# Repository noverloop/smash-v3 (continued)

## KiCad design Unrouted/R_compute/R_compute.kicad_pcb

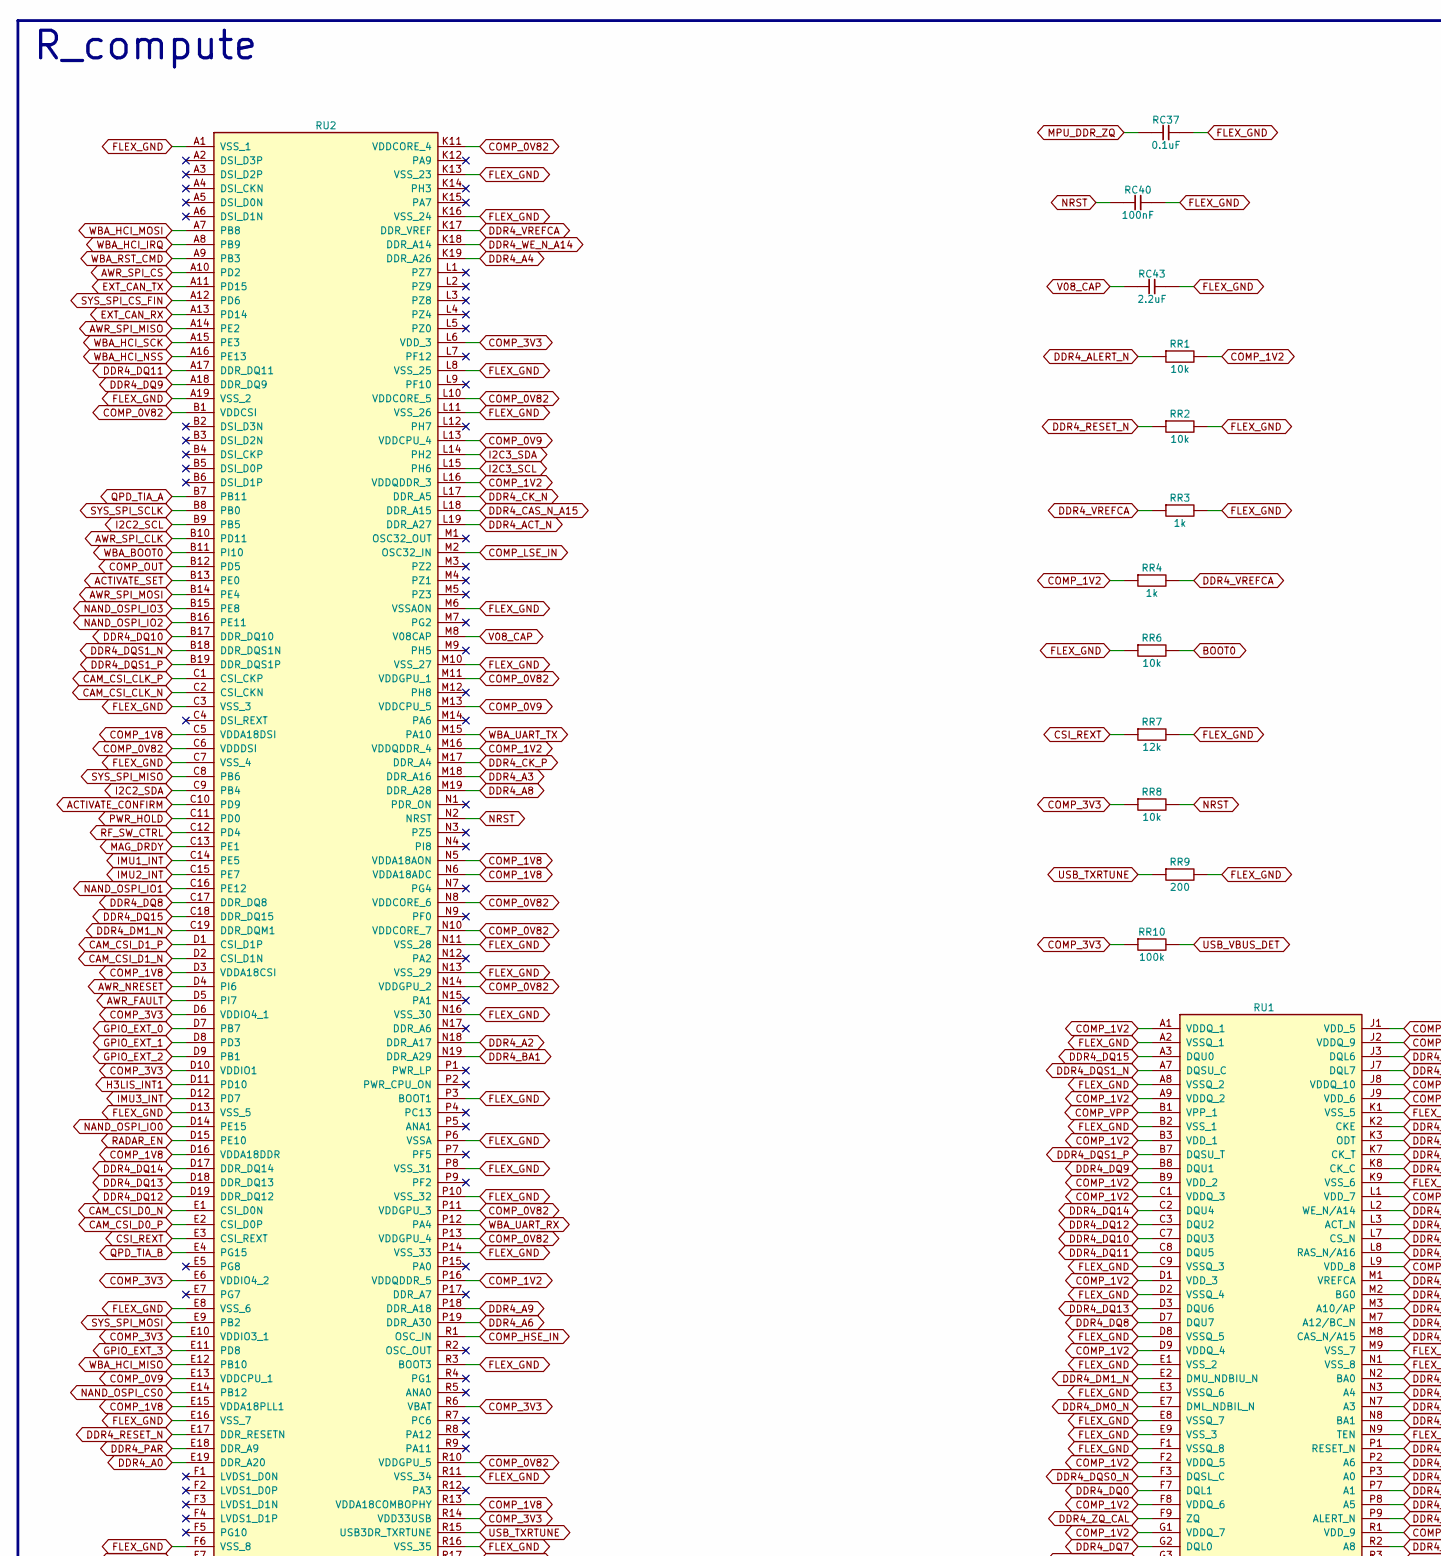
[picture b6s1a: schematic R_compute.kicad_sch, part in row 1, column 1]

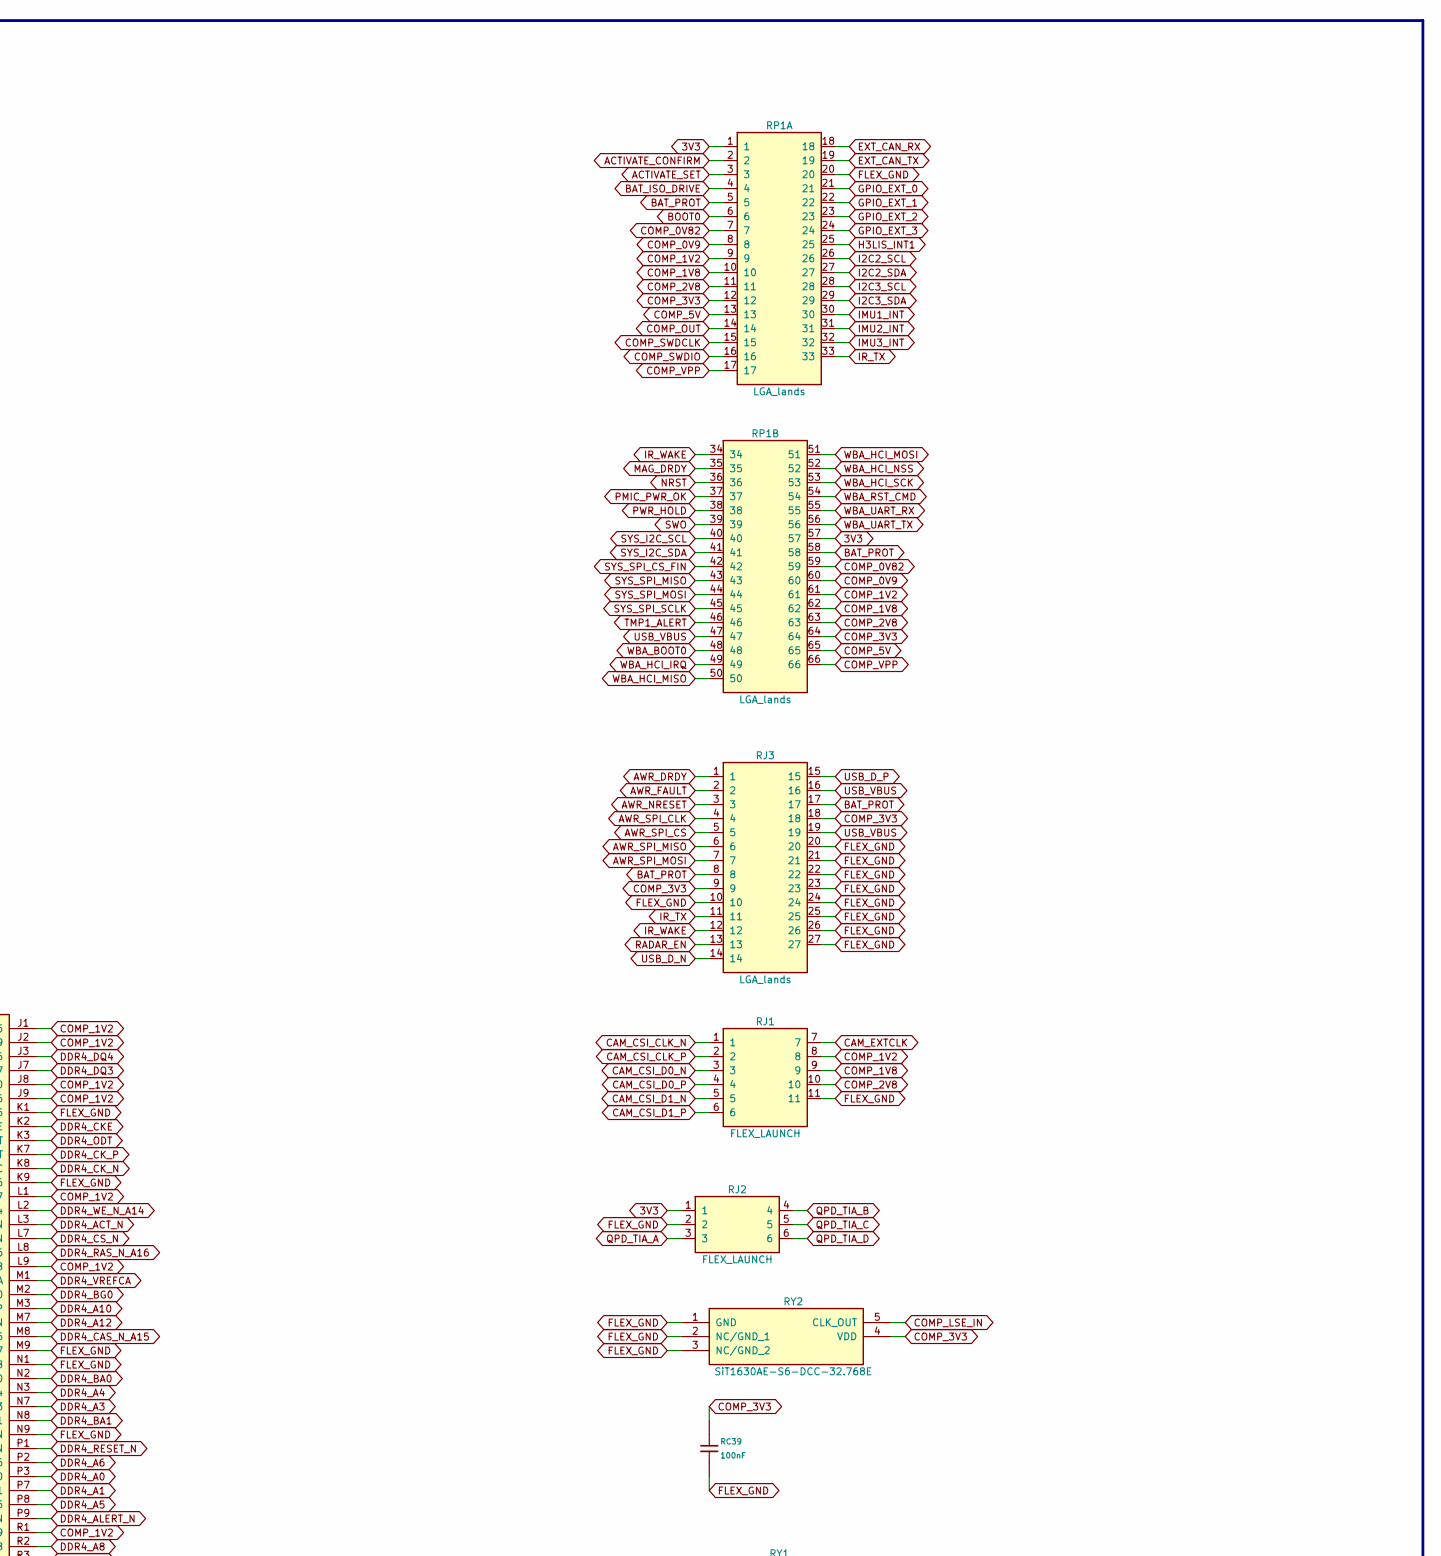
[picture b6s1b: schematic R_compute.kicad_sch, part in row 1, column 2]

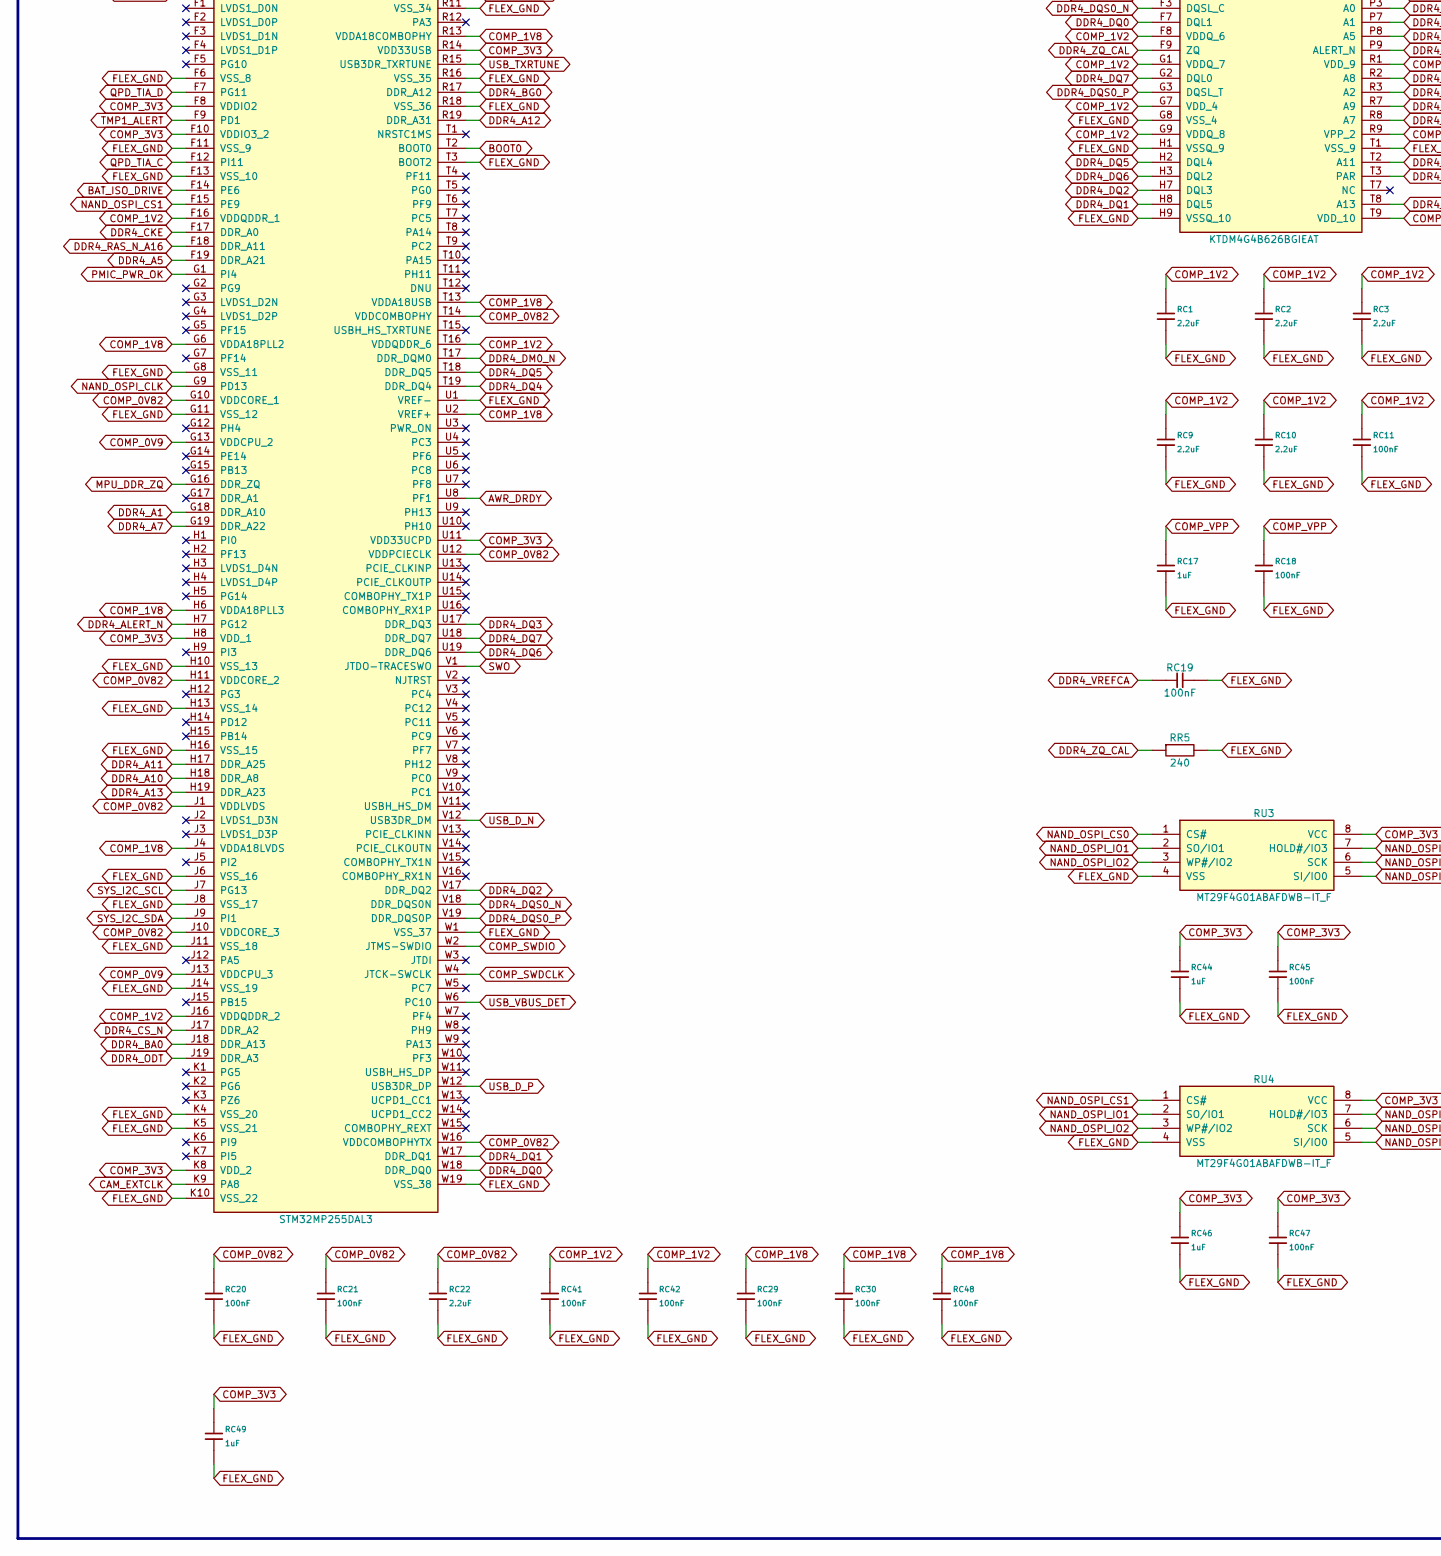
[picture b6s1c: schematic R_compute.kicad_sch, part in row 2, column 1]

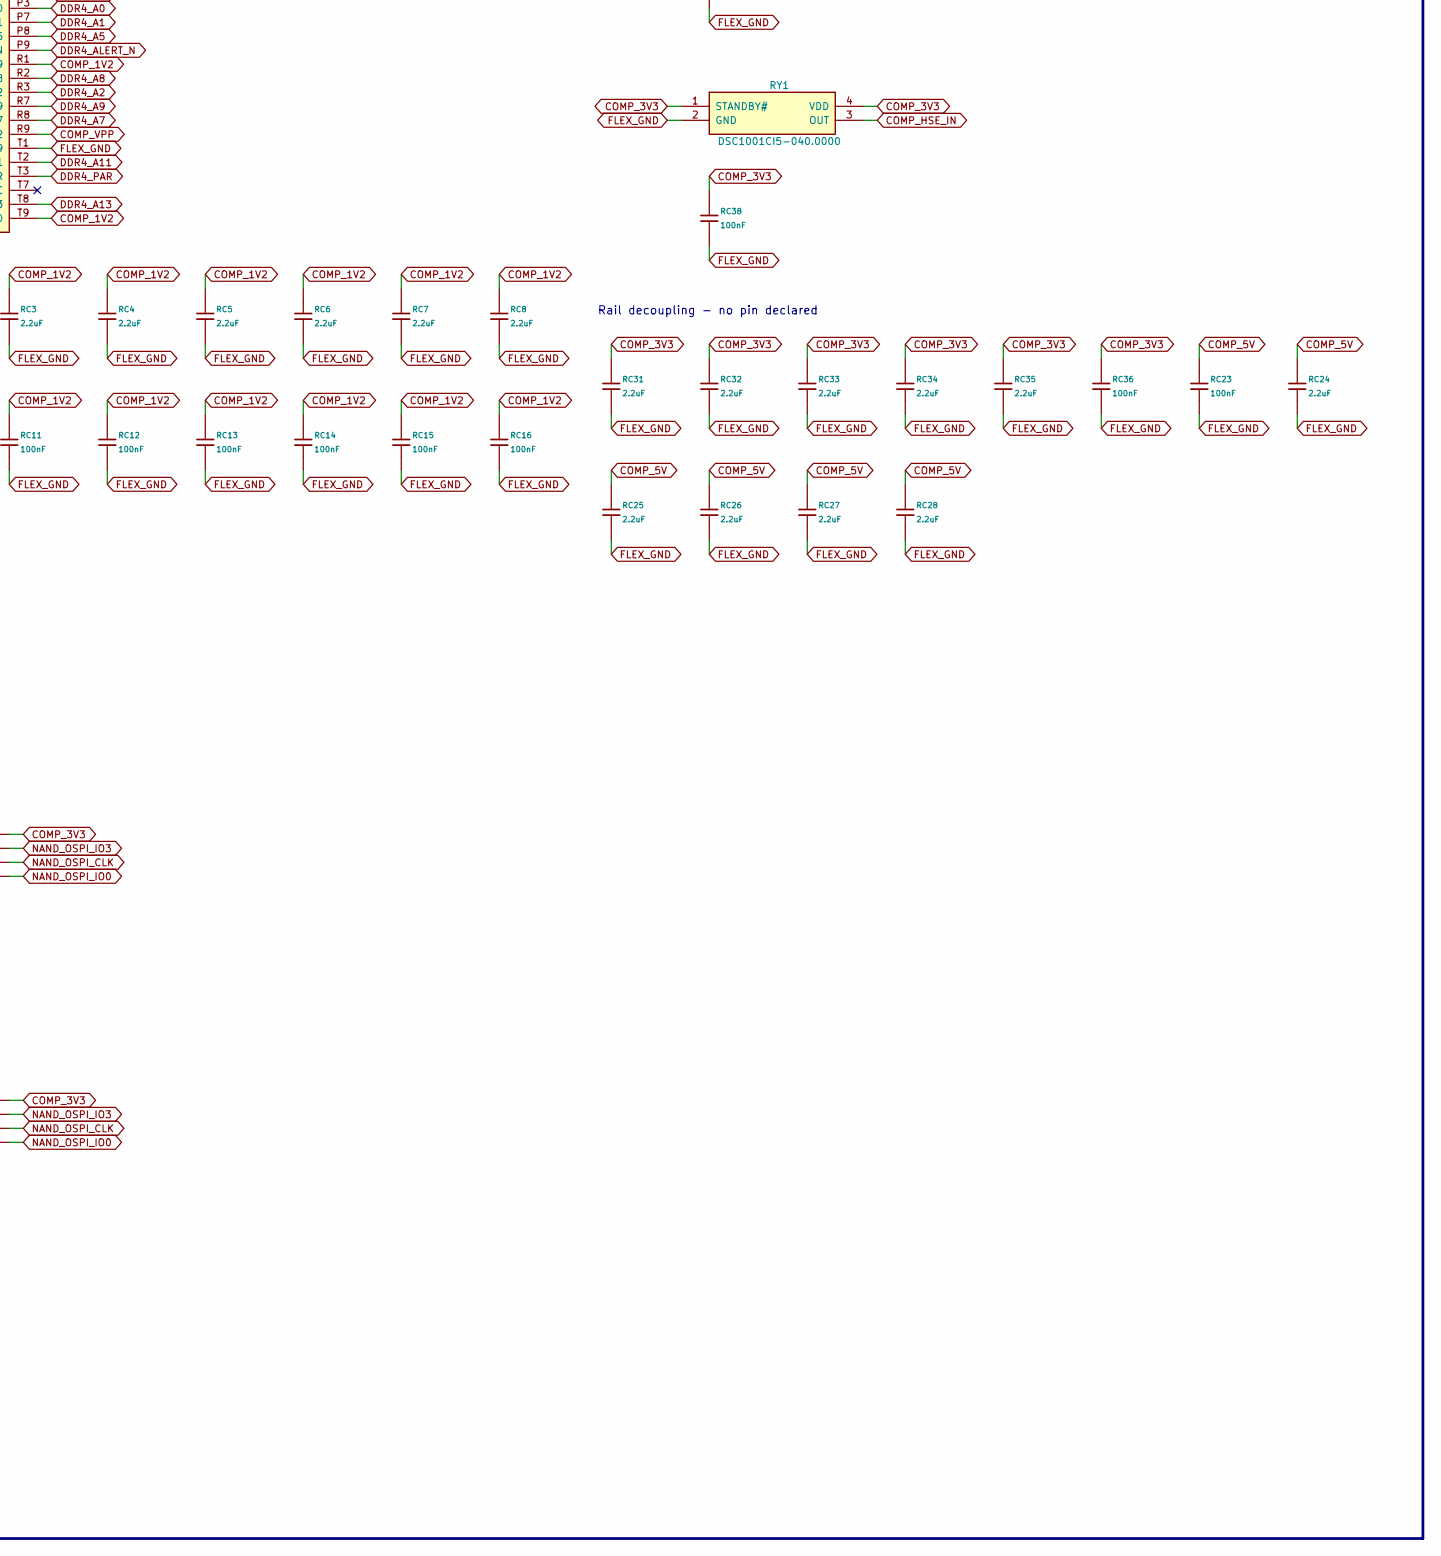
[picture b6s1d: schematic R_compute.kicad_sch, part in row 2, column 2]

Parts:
RC1, RC2, RC3, RC4, RC5, RC6, RC7, RC8, RC9, RC10, RC22, RC24, RC25, RC26, RC27, RC28, RC31, RC32, RC33, RC34, RC35, RC43: 2.2uF; Capacitor_SMD_C_0603_1608Metric; MPN C-Series MIL-PRF-32535 X7R 0603 2.2uF
RC11, RC12, RC13, RC14, RC15, RC16, RC18, RC19, RC20, RC21, RC23, RC29, RC30, RC36, RC38, RC39, RC40, RC41, RC42, RC45, RC47, RC48: 100nF; Capacitor_SMD_C_0402_1005Metric; MPN C0402 X7R 100nF
RC17, RC44, RC46, RC49: 1uF; Capacitor_SMD_C_0805_2012Metric; MPN C-Series MIL-PRF-32535 X7R 0805 1uF
RC37: 0.1uF; Capacitor_SMD_C_0402_1005Metric; MPN C0402 X7R 0.1uF
RJ1: FLEX_LAUNCH; J_FLEXL_companion_compute__camera_module; MPN FLEX_LAUNCH
RJ2: FLEX_LAUNCH; J_FLEXL_companion_compute__qpd_module; MPN FLEX_LAUNCH
RJ3: LGA_lands; J_companion_compute_spacer_companion_compute_radar_module; MPN LGA_lands
RP1: LGA_lands; P_companion_compute_spacer_power_board_companion_compute; MPN LGA_lands
RR1, RR2, RR6, RR8: 10k; Resistor_SMD_R_0402_1005Metric; MPN CRCW0402 10k 1% e3
RR3, RR4: 1k; Resistor_SMD_R_0402_1005Metric; MPN CRCW0402 1k 1% e3
RR5: 240; Resistor_SMD_R_0402_1005Metric; MPN CRCW0402 240 1% e3
RR7: 12k; Resistor_SMD_R_0402_1005Metric; MPN CRCW0402 12k 1% e3
RR9: 200; Resistor_SMD_R_0402_1005Metric; MPN CRCW0402 200 1% e3
RR10: 100k; Resistor_SMD_R_0402_1005Metric; MPN CRCW0402 100k 1% e3
RU1: KTDM4G4B626BGIEAT; BGA96C80P9X16_750X1300X100; MPN KTDM4G4B626BGIEAT
RU2: STM32MP255DAL3; MPN STM32MP255DAL3
RU3, RU4: MT29F4G01ABAFDWB-IT_F; SON127P800X600X65-8N; MPN MT29F4G01ABAFDWB-IT_F
RY1: DSC1001CI5-040.0000; DSC1001CI50080000; MPN DSC1001CI5-040.0000
RY2: SiT1630AE-S6-DCC-32.768E; SOT-23_5pins; MPN SiT1630AE-S6-DCC-32.768E

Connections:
3V3: RJ2.1, RP1.1, RP1.57
ACTIVATE_CONFIRM: RP1.2, RU2.C10 (PD9)
ACTIVATE_SET: RP1.3, RU2.B13 (PE0)
AWR_DRDY: RJ3.1, RU2.U8 (PF1)
AWR_FAULT: RJ3.2, RU2.D5 (PI7)
AWR_NRESET: RJ3.3, RU2.D4 (PI6)
AWR_SPI_CLK: RJ3.4, RU2.B10 (PD11)
AWR_SPI_CS: RJ3.5, RU2.A10 (PD2)
AWR_SPI_MISO: RJ3.6, RU2.A14 (PE2)
AWR_SPI_MOSI: RJ3.7, RU2.B14 (PE4)
BAT_ISO_DRIVE: RP1.4, RU2.F14 (PE6)
BAT_PROT: RJ3.8, RJ3.17, RP1.5, RP1.58
BOOT0: RP1.6, RR6.2, RU2.T2 (BOOT0)
CAM_CSI_CLK_N: RJ1.1, RU2.C2 (CSI_CKN)
CAM_CSI_CLK_P: RJ1.2, RU2.C1 (CSI_CKP)
CAM_CSI_D0_N: RJ1.3, RU2.E1 (CSI_D0N)
CAM_CSI_D0_P: RJ1.4, RU2.E2 (CSI_D0P)
CAM_CSI_D1_N: RJ1.5, RU2.D2 (CSI_D1N)
CAM_CSI_D1_P: RJ1.6, RU2.D1 (CSI_D1P)
CAM_EXTCLK: RJ1.7, RU2.K9 (PA8)
COMP_0V9: RP1.8, RP1.60, RU2.E13 (VDDCPU_1), RU2.G13 (VDDCPU_2), RU2.J13 (VDDCPU_3), RU2.L13 (VDDCPU_4), RU2.M13 (VDDCPU_5)
COMP_0V82: RC20.1, RC21.1, RC22.1, RP1.7, RP1.59, RU2.B1 (VDDCSI), RU2.C6 (VDDDSI), RU2.G10 (VDDCORE_1), RU2.H11 (VDDCORE_2), RU2.J1 (VDDLVDS), RU2.J10 (VDDCORE_3), RU2.K11 (VDDCORE_4), RU2.L10 (VDDCORE_5), RU2.M11 (VDDGPU_1), RU2.N8 (VDDCORE_6), RU2.N10 (VDDCORE_7), RU2.N14 (VDDGPU_2), RU2.P11 (VDDGPU_3), RU2.P13 (VDDGPU_4), RU2.R10 (VDDGPU_5), RU2.T14 (VDDCOMBOPHY), RU2.U12 (VDDPCIECLK), RU2.W16 (VDDCOMBOPHYTX)
COMP_1V2: RC1.1, RC2.1, RC3.1, RC4.1, RC5.1, RC6.1, RC7.1, RC8.1, RC9.1, RC10.1, RC11.1, RC12.1, RC13.1, RC14.1, RC15.1, RC16.1, RC41.1, RC42.1, RJ1.8, RP1.9, RP1.61, RR1.2, RR4.1, RU1.A1 (VDDQ_1), RU1.A9 (VDDQ_2), RU1.B3 (VDD_1), RU1.B9 (VDD_2), RU1.C1 (VDDQ_3), RU1.D1 (VDD_3), RU1.D9 (VDDQ_4), RU1.F2 (VDDQ_5), RU1.F8 (VDDQ_6), RU1.G1 (VDDQ_7), RU1.G7 (VDD_4), RU1.G9 (VDDQ_8), RU1.J1 (VDD_5), RU1.J2 (VDDQ_9), RU1.J8 (VDDQ_10), RU1.J9 (VDD_6), RU1.L1 (VDD_7), RU1.L9 (VDD_8), RU1.R1 (VDD_9), RU1.T9 (VDD_10), RU2.F16 (VDDQDDR_1), RU2.J16 (VDDQDDR_2), RU2.L16 (VDDQDDR_3), RU2.M16 (VDDQDDR_4), RU2.P16 (VDDQDDR_5), RU2.T16 (VDDQDDR_6)
COMP_1V8: RC29.1, RC30.1, RC48.1, RJ1.9, RP1.10, RP1.62, RU2.C5 (VDDA18DSI), RU2.D3 (VDDA18CSI), RU2.D16 (VDDA18DDR), RU2.E15 (VDDA18PLL1), RU2.G6 (VDDA18PLL2), RU2.H6 (VDDA18PLL3), RU2.J4 (VDDA18LVDS), RU2.N5 (VDDA18AON), RU2.N6 (VDDA18ADC), RU2.R13 (VDDA18COMBOPHY), RU2.T13 (VDDA18USB), RU2.U2 (VREF+)
COMP_2V8: RJ1.10, RP1.11, RP1.63
COMP_3V3: RC31.1, RC32.1, RC33.1, RC34.1, RC35.1, RC36.1, RC38.1, RC39.1, RC44.1, RC45.1, RC46.1, RC47.1, RC49.1, RJ3.9, RJ3.18, RP1.12, RP1.64, RR8.1, RR10.1, RU2.D6 (VDDIO4_1), RU2.D10 (VDDIO1), RU2.E6 (VDDIO4_2), RU2.E10 (VDDIO3_1), RU2.F8 (VDDIO2), RU2.F10 (VDDIO3_2), RU2.H8 (VDD_1), RU2.K8 (VDD_2), RU2.L6 (VDD_3), RU2.R6 (VBAT), RU2.R14 (VDD33USB), RU2.U11 (VDD33UCPD), RU3.8 (VCC), RU4.8 (VCC), RY1.1 (STANDBY#), RY1.4 (VDD), RY2.4 (VDD)
COMP_5V: RC23.1, RC24.1, RC25.1, RC26.1, RC27.1, RC28.1, RP1.13, RP1.65
COMP_HSE_IN: RU2.R1 (OSC_IN), RY1.3 (OUT)
COMP_LSE_IN: RU2.M2 (OSC32_IN), RY2.5 (CLK_OUT)
COMP_OUT: RP1.14, RU2.B12 (PD5)
COMP_SWDCLK: RP1.15, RU2.W4 (JTCK-SWCLK)
COMP_SWDIO: RP1.16, RU2.W2 (JTMS-SWDIO)
COMP_VPP: RC17.1, RC18.1, RP1.17, RP1.66, RU1.B1 (VPP_1), RU1.R9 (VPP_2)
CSI_REXT: RR7.1, RU2.E3 (CSI_REXT)
DDR4_A0: RU1.P3 (A0), RU2.E19 (DDR_A20)
DDR4_A1: RU1.P7 (A1), RU2.G18 (DDR_A10)
DDR4_A2: RU1.R3 (A2), RU2.N18 (DDR_A17)
DDR4_A3: RU1.N7 (A3), RU2.M18 (DDR_A16)
DDR4_A4: RU1.N3 (A4), RU2.K19 (DDR_A26)
DDR4_A5: RU1.P8 (A5), RU2.F19 (DDR_A21)
DDR4_A6: RU1.P2 (A6), RU2.P19 (DDR_A30)
DDR4_A7: RU1.R8 (A7), RU2.G19 (DDR_A22)
DDR4_A8: RU1.R2 (A8), RU2.M19 (DDR_A28)
DDR4_A9: RU1.R7 (A9), RU2.P18 (DDR_A18)
DDR4_A10: RU1.M3 (A10/AP), RU2.H18 (DDR_A8)
DDR4_A11: RU1.T2 (A11), RU2.H17 (DDR_A25)
DDR4_A12: RU1.M7 (A12/BC_N), RU2.R19 (DDR_A31)
DDR4_A13: RU1.T8 (A13), RU2.H19 (DDR_A23)
DDR4_ACT_N: RU1.L3 (ACT_N), RU2.L19 (DDR_A27)
DDR4_ALERT_N: RR1.1, RU1.P9 (ALERT_N), RU2.H7 (PG12)
DDR4_BA0: RU1.N2 (BA0), RU2.J18 (DDR_A13)
DDR4_BA1: RU1.N8 (BA1), RU2.N19 (DDR_A29)
DDR4_BG0: RU1.M2 (BG0), RU2.R17 (DDR_A12)
DDR4_CAS_N_A15: RU1.M8 (CAS_N/A15), RU2.L18 (DDR_A15)
DDR4_CKE: RU1.K2 (CKE), RU2.F17 (DDR_A0)
DDR4_CK_N: RU1.K8 (CK_C), RU2.L17 (DDR_A5)
DDR4_CK_P: RU1.K7 (CK_T), RU2.M17 (DDR_A4)
DDR4_CS_N: RU1.L7 (CS_N), RU2.J17 (DDR_A2)
DDR4_DM0_N: RU1.E7 (DML_NDBIL_N), RU2.T17 (DDR_DQM0)
DDR4_DM1_N: RU1.E2 (DMU_NDBIU_N), RU2.C19 (DDR_DQM1)
DDR4_DQ0: RU1.F7 (DQL1), RU2.W18 (DDR_DQ0)
DDR4_DQ1: RU1.H8 (DQL5), RU2.W17 (DDR_DQ1)
DDR4_DQ2: RU1.H7 (DQL3), RU2.V17 (DDR_DQ2)
DDR4_DQ3: RU1.J7 (DQL7), RU2.U17 (DDR_DQ3)
DDR4_DQ4: RU1.J3 (DQL6), RU2.T19 (DDR_DQ4)
DDR4_DQ5: RU1.H2 (DQL4), RU2.T18 (DDR_DQ5)
DDR4_DQ6: RU1.H3 (DQL2), RU2.U19 (DDR_DQ6)
DDR4_DQ7: RU1.G2 (DQL0), RU2.U18 (DDR_DQ7)
DDR4_DQ8: RU1.D7 (DQU7), RU2.C17 (DDR_DQ8)
DDR4_DQ9: RU1.B8 (DQU1), RU2.A18 (DDR_DQ9)
DDR4_DQ10: RU1.C7 (DQU3), RU2.B17 (DDR_DQ10)
DDR4_DQ11: RU1.C8 (DQU5), RU2.A17 (DDR_DQ11)
DDR4_DQ12: RU1.C3 (DQU2), RU2.D19 (DDR_DQ12)
DDR4_DQ13: RU1.D3 (DQU6), RU2.D18 (DDR_DQ13)
DDR4_DQ14: RU1.C2 (DQU4), RU2.D17 (DDR_DQ14)
DDR4_DQ15: RU1.A3 (DQU0), RU2.C18 (DDR_DQ15)
DDR4_DQS0_N: RU1.F3 (DQSL_C), RU2.V18 (DDR_DQS0N)
DDR4_DQS0_P: RU1.G3 (DQSL_T), RU2.V19 (DDR_DQS0P)
DDR4_DQS1_N: RU1.A7 (DQSU_C), RU2.B18 (DDR_DQS1N)
DDR4_DQS1_P: RU1.B7 (DQSU_T), RU2.B19 (DDR_DQS1P)
DDR4_ODT: RU1.K3 (ODT), RU2.J19 (DDR_A3)
DDR4_PAR: RU1.T3 (PAR), RU2.E18 (DDR_A9)
DDR4_RAS_N_A16: RU1.L8 (RAS_N/A16), RU2.F18 (DDR_A11)
DDR4_RESET_N: RR2.1, RU1.P1 (RESET_N), RU2.E17 (DDR_RESETN)
DDR4_VREFCA: RC19.1, RR3.1, RR4.2, RU1.M1 (VREFCA), RU2.K17 (DDR_VREF)
DDR4_WE_N_A14: RU1.L2 (WE_N/A14), RU2.K18 (DDR_A14)
DDR4_ZQ_CAL: RR5.1, RU1.F9 (ZQ)
EXT_CAN_RX: RP1.18, RU2.A13 (PD14)
EXT_CAN_TX: RP1.19, RU2.A11 (PD15)
FLEX_GND: RC1.2, RC2.2, RC3.2, RC4.2, RC5.2, RC6.2, RC7.2, RC8.2, RC9.2, RC10.2, RC11.2, RC12.2, RC13.2, RC14.2, RC15.2, RC16.2, RC17.2, RC18.2, RC19.2, RC20.2, RC21.2, RC22.2, RC23.2, RC24.2, RC25.2, RC26.2, RC27.2, RC28.2, RC29.2, RC30.2, RC31.2, RC32.2, RC33.2, RC34.2, RC35.2, RC36.2, RC37.2, RC38.2, RC39.2, RC40.2, RC41.2, RC42.2, RC43.2, RC44.2, RC45.2, RC46.2, RC47.2, RC48.2, RC49.2, RJ1.11, RJ2.2, RJ3.10, RJ3.20, RJ3.21, RJ3.22, RJ3.23, RJ3.24, RJ3.25, RJ3.26, RJ3.27, RP1.20, RR2.2, RR3.2, RR5.2, RR6.1, RR7.2, RR9.2, RU1.A2 (VSSQ_1), RU1.A8 (VSSQ_2), RU1.B2 (VSS_1), RU1.C9 (VSSQ_3), RU1.D2 (VSSQ_4), RU1.D8 (VSSQ_5), RU1.E1 (VSS_2), RU1.E3 (VSSQ_6), RU1.E8 (VSSQ_7), RU1.E9 (VSS_3), RU1.F1 (VSSQ_8), RU1.G8 (VSS_4), RU1.H1 (VSSQ_9), RU1.H9 (VSSQ_10), RU1.K1 (VSS_5), RU1.K9 (VSS_6), RU1.M9 (VSS_7), RU1.N1 (VSS_8), RU1.N9 (TEN), RU1.T1 (VSS_9), RU2.A1 (VSS_1), RU2.A19 (VSS_2), RU2.C3 (VSS_3), RU2.C7 (VSS_4), RU2.D13 (VSS_5), RU2.E8 (VSS_6), RU2.E16 (VSS_7), RU2.F6 (VSS_8), RU2.F11 (VSS_9), RU2.F13 (VSS_10), RU2.G8 (VSS_11), RU2.G11 (VSS_12), RU2.H10 (VSS_13), RU2.H13 (VSS_14), RU2.H16 (VSS_15), RU2.J6 (VSS_16), RU2.J8 (VSS_17), RU2.J11 (VSS_18), RU2.J14 (VSS_19), RU2.K4 (VSS_20), RU2.K5 (VSS_21), RU2.K10 (VSS_22), RU2.K13 (VSS_23), RU2.K16 (VSS_24), RU2.L8 (VSS_25), RU2.L11 (VSS_26), RU2.M6 (VSSAON), RU2.M10 (VSS_27), RU2.N11 (VSS_28), RU2.N13 (VSS_29), RU2.N16 (VSS_30), RU2.P3 (BOOT1), RU2.P6 (VSSA), RU2.P8 (VSS_31), RU2.P10 (VSS_32), RU2.P14 (VSS_33), RU2.R3 (BOOT3), RU2.R11 (VSS_34), RU2.R16 (VSS_35), RU2.R18 (VSS_36), RU2.T3 (BOOT2), RU2.U1 (VREF-), RU2.W1 (VSS_37), RU2.W19 (VSS_38), RU3.4 (VSS), RU4.4 (VSS), RY1.2 (GND), RY2.1 (GND), RY2.2 (NC/GND_1), RY2.3 (NC/GND_2)
GPIO_EXT_0: RP1.21, RU2.D7 (PB7)
GPIO_EXT_1: RP1.22, RU2.D8 (PD3)
GPIO_EXT_2: RP1.23, RU2.D9 (PB1)
GPIO_EXT_3: RP1.24, RU2.E11 (PD8)
H3LIS_INT1: RP1.25, RU2.D11 (PD10)
I2C2_SCL: RP1.26, RU2.B9 (PB5)
I2C2_SDA: RP1.27, RU2.C9 (PB4)
I2C3_SCL: RP1.28, RU2.L15 (PH6)
I2C3_SDA: RP1.29, RU2.L14 (PH2)
IMU1_INT: RP1.30, RU2.C14 (PE5)
IMU2_INT: RP1.31, RU2.C15 (PE7)
IMU3_INT: RP1.32, RU2.D12 (PD7)
IR_TX: RJ3.11, RP1.33
IR_WAKE: RJ3.12, RP1.34
MAG_DRDY: RP1.35, RU2.C13 (PE1)
MPU_DDR_ZQ: RC37.1, RU2.G16 (DDR_ZQ)
NAND_OSPI_CLK: RU2.G9 (PD13), RU3.6 (SCK), RU4.6 (SCK)
NAND_OSPI_CS0: RU2.E14 (PB12), RU3.1 (CS#)
NAND_OSPI_CS1: RU2.F15 (PE9), RU4.1 (CS#)
NAND_OSPI_IO0: RU2.D14 (PE15), RU3.5 (SI/IO0), RU4.5 (SI/IO0)
NAND_OSPI_IO1: RU2.C16 (PE12), RU3.2 (SO/IO1), RU4.2 (SO/IO1)
NAND_OSPI_IO2: RU2.B16 (PE11), RU3.3 (WP#/IO2), RU4.3 (WP#/IO2)
NAND_OSPI_IO3: RU2.B15 (PE8), RU3.7 (HOLD#/IO3), RU4.7 (HOLD#/IO3)
NRST: RC40.1, RP1.36, RR8.2, RU2.N2 (NRST)
PMIC_PWR_OK: RP1.37, RU2.G1 (PI4)
PWR_HOLD: RP1.38, RU2.C11 (PD0)
QPD_TIA_A: RJ2.3, RU2.B7 (PB11)
QPD_TIA_B: RJ2.4, RU2.E4 (PG15)
QPD_TIA_C: RJ2.5, RU2.F12 (PI11)
QPD_TIA_D: RJ2.6, RU2.F7 (PG11)
RADAR_EN: RJ3.13, RU2.D15 (PE10)
RF_SW_CTRL: RU2.C12 (PD4)
SWO: RP1.39, RU2.V1 (JTDO-TRACESWO)
SYS_I2C_SCL: RP1.40, RU2.J7 (PG13)
SYS_I2C_SDA: RP1.41, RU2.J9 (PI1)
SYS_SPI_CS_FIN: RP1.42, RU2.A12 (PD6)
SYS_SPI_MISO: RP1.43, RU2.C8 (PB6)
SYS_SPI_MOSI: RP1.44, RU2.E9 (PB2)
SYS_SPI_SCLK: RP1.45, RU2.B8 (PB0)
TMP1_ALERT: RP1.46, RU2.F9 (PD1)
USB_D_N: RJ3.14, RU2.V12 (USB3DR_DM)
USB_D_P: RJ3.15, RU2.W12 (USB3DR_DP)
USB_TXRTUNE: RR9.1, RU2.R15 (USB3DR_TXRTUNE)
USB_VBUS: RJ3.16, RJ3.19, RP1.47
USB_VBUS_DET: RR10.2, RU2.W6 (PC10)
V08_CAP: RC43.1, RU2.M8 (V08CAP)
WBA_BOOT0: RP1.48, RU2.B11 (PI10)
WBA_HCI_IRQ: RP1.49, RU2.A8 (PB9)
WBA_HCI_MISO: RP1.50, RU2.E12 (PB10)
WBA_HCI_MOSI: RP1.51, RU2.A7 (PB8)
WBA_HCI_NSS: RP1.52, RU2.A16 (PE13)
WBA_HCI_SCK: RP1.53, RU2.A15 (PE3)
WBA_RST_CMD: RP1.54, RU2.A9 (PB3)
WBA_UART_RX: RP1.55, RU2.P12 (PA4)
WBA_UART_TX: RP1.56, RU2.M15 (PA10)

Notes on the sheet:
R_compute
Rail decoupling - no pin declared

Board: 20 copper layers, 71 parts (62 on the bottom side), 144 nets, no tracks yet.

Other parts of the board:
RMH1, RMH2: smash_mech_potting

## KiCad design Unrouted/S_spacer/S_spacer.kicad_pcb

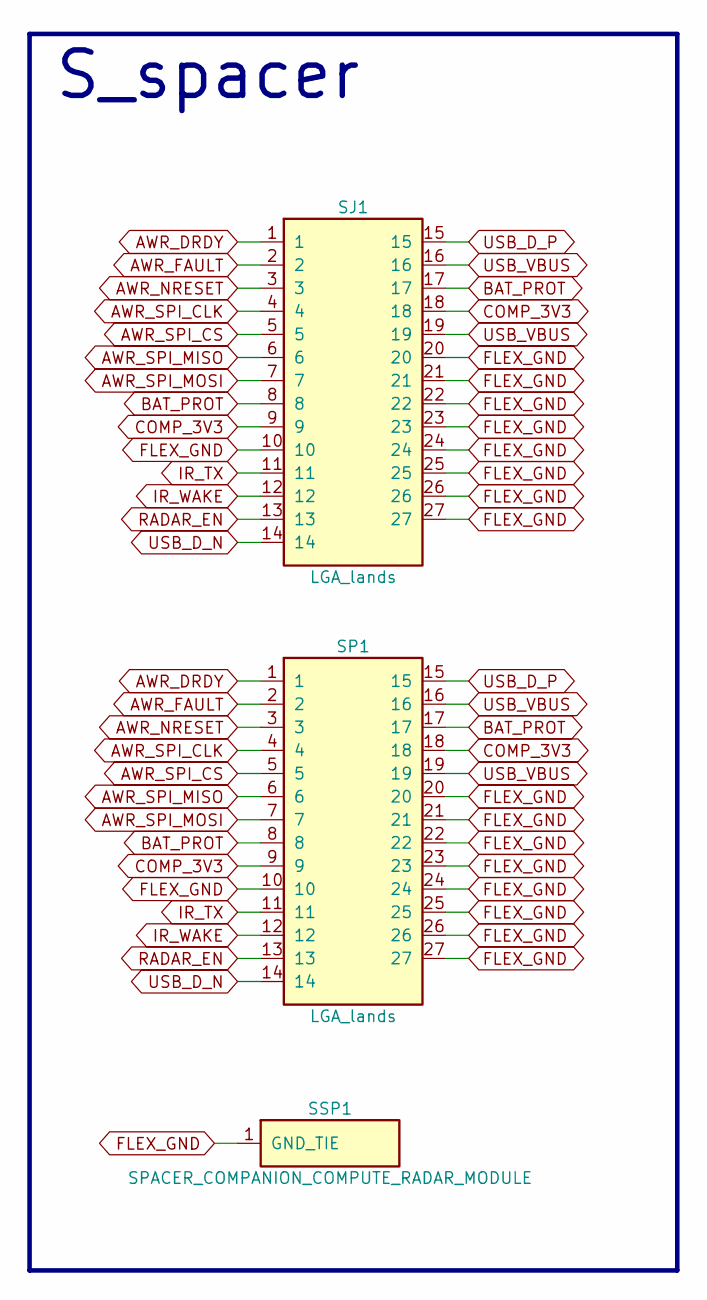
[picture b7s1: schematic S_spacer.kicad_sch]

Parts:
SJ1: LGA_lands; J_spacer_companion_compute_radar_module_top; MPN LGA_lands
SP1: LGA_lands; P_spacer_companion_compute_radar_module_bot; MPN LGA_lands
SSP1: SPACER_COMPANION_COMPUTE_RADAR_MODULE; Spacer_Mechanical_34mm

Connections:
AWR_DRDY: SJ1.1, SP1.1
AWR_FAULT: SJ1.2, SP1.2
AWR_NRESET: SJ1.3, SP1.3
AWR_SPI_CLK: SJ1.4, SP1.4
AWR_SPI_CS: SJ1.5, SP1.5
AWR_SPI_MISO: SJ1.6, SP1.6
AWR_SPI_MOSI: SJ1.7, SP1.7
BAT_PROT: SJ1.8, SJ1.17, SP1.8, SP1.17
COMP_3V3: SJ1.9, SJ1.18, SP1.9, SP1.18
FLEX_GND: SJ1.10, SJ1.20, SJ1.21, SJ1.22, SJ1.23, SJ1.24, SJ1.25, SJ1.26, SJ1.27, SP1.10, SP1.20, SP1.21, SP1.22, SP1.23, SP1.24, SP1.25, SP1.26, SP1.27, SSP1.1
IR_TX: SJ1.11, SP1.11
IR_WAKE: SJ1.12, SP1.12
RADAR_EN: SJ1.13, SP1.13
USB_D_N: SJ1.14, SP1.14
USB_D_P: SJ1.15, SP1.15
USB_VBUS: SJ1.16, SJ1.19, SP1.16, SP1.19

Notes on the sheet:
S_spacer

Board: 2 copper layers, 5 parts (1 on the bottom side), 16 nets, no tracks yet.

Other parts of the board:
SMH1, SMH2: smash_mech_potting
